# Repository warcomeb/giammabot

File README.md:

# giammabot
GiammaBot - Our family battle robot! :)

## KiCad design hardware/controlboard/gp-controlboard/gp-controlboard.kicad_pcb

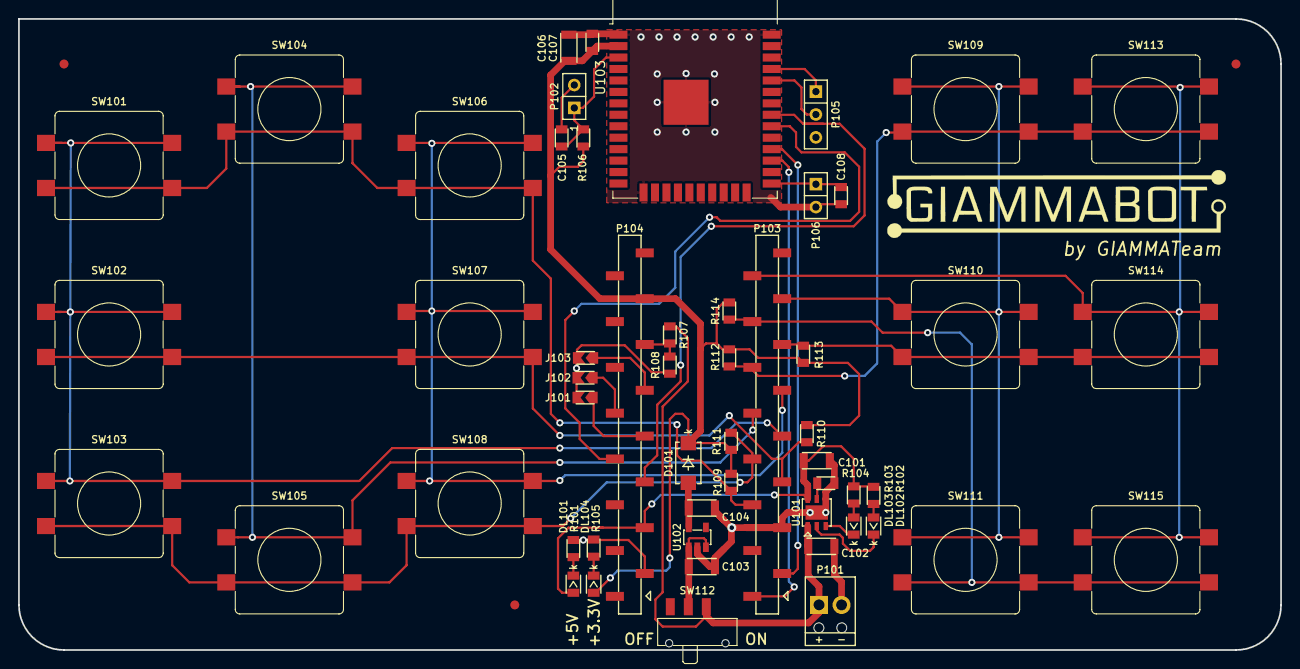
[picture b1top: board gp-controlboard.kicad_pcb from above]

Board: 2 copper layers, 140.0 x 70.0 mm, 57 parts (0 on the bottom side), 36 nets.

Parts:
C101, C102: 4u7; CAPACITOR-1206
C103, C104: 1u; CAPACITOR-1206
C105, C107, C108: 100n; CAPACITOR-0805
C106: 10u; CAPACITOR-1206
D101: MBRA340T3G; DIODE-DO214AC-UNI
DL101, DL104: GREEN; LED-0805
DL102, DL103: RED; LED-0805
J101, J102, J103: JUMPER-2_1; JUMPERSMD-2-0805
P101: BATTERY; CONN-MPT0.5_2-2.54
P102: EN_JMP; CONN-STRIP-2x1-2.54
P103: NUCLEO-CN3; SOCKET_16x1_2.54_SMD-WE-61001611921
P104: NUCLEO-CN4; SOCKET_16x1_2.54_SMD-WE-61001611921
P105: ESP_PROG; CONN-STRIP-3x1-2.54
P106: BOOT_JMP; CONN-STRIP-2x1-2.54
R101, R105: 330; RESISTOR-0805
R102, R103: 270; RESISTOR-0805
R104, R107, R108: TBD; RESISTOR-0805
R106, R109, R110, R111, R112, R113, R114: 10k; RESISTOR-0805
SW101, SW102, SW103, SW104, SW105, SW106, SW107, SW108, SW109, SW110, SW111, SW113, SW114, SW115: 430162073826; BUTTON-WE-430162073826
SW112: 450405020524; SWITCH-SPDT-WURTH-450405020524
U101: STBC08PMR; DFN6_3.0x3.0_1.0
U102: TLV70233DBV; SOT23-5
U103: ESP32-WROOM-32E(8MB); ESP32-WROOM-32D
VAL**: FIDUCIALMARK_1MM_3MM
VAL**#2, VAL**#3: FIDUCIALMARK_1MM_3MM

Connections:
+3.3V: C106.2, C107.1, D101.1, DL104.1, P104.14, R106.1, R109.1, R110.1, R111.1, R112.1, R113.1, R114.1, U103.2
+5V: C101.1, DL101.1, P104.4, R102.1, R103.1, U101.6
+VBAT: C102.1, P101.1, R107.2, SW112.3, U101.1
/ADC_BAT_STATUS: P104.12, R107.1, R108.2
/ADDR_0: J101.2, P104.8
/ADDR_1: J102.2, P104.9
/ADDR_2: J103.2, P104.10
/DIRECTION_C1: P103.8, SW101.1, SW101.2, SW102.1, SW102.2, SW103.1, SW103.2
/DIRECTION_C2: P103.9, SW104.1, SW104.2, SW105.1, SW105.2
/DIRECTION_C3: P103.10, SW106.1, SW106.2, SW107.1, SW107.2, SW108.1, SW108.2
/DIRECTION_R1: P103.5, R109.2, SW101.3, SW101.4, SW104.3, SW104.4, SW106.3, SW106.4
/DIRECTION_R2: P103.6, R110.2, SW102.3, SW102.4, SW107.3, SW107.4
/DIRECTION_R3: P103.7, R111.2, SW103.3, SW103.4, SW105.3, SW105.4, SW108.3, SW108.4
/ESP2MCU_01: P104.6, U103.31
/ESP2MCU_02: P104.7, U103.30
/ESP_BOOT: C108.2, P106.1, U103.25
/ESP_ENABLE: C105.2, P102.1, R106.2, U103.3
/ESP_PROG_RX: P105.2, U103.34
/ESP_PROG_TX: P105.1, U103.35
/POWER_C1: P103.14, SW109.1, SW109.2, SW110.1, SW110.2, SW111.1, SW111.2
/POWER_C2: P103.15, SW113.1, SW113.2, SW114.1, SW114.2, SW115.1, SW115.2
/POWER_R1: P103.11, R112.2, SW109.3, SW109.4, SW113.3, SW113.4
/POWER_R2: P103.12, R113.2, SW110.3, SW110.4, SW114.3, SW114.4
/POWER_R3: P103.13, R114.2, SW111.3, SW111.4, SW115.3, SW115.4
/UART_CMD_RX: P103.2, U103.28
/UART_CMD_TX: P103.1, U103.27
GND: C101.2, C102.2, C103.2, C104.2, C105.1, C106.1, C107.2, C108.1, J101.1, J102.1, J103.1, P101.2, P102.2, P103.4, P104.2, P105.3, P106.2, R101.1, R104.2, R105.1, R108.1, U101.4, U101.7, U102.2, U103.1, U103.15, U103.38, U103.39
unnamed: C103.1, SW112.2, U102.1, U102.3
unnamed: C104.1, D101.2, U102.5
unnamed: DL101.2, R101.2
unnamed: DL102.1, R102.2
unnamed: DL102.2, U101.2
unnamed: DL103.1, R103.2
unnamed: DL103.2, U101.3
unnamed: DL104.2, R105.2
unnamed: R104.1, U101.5

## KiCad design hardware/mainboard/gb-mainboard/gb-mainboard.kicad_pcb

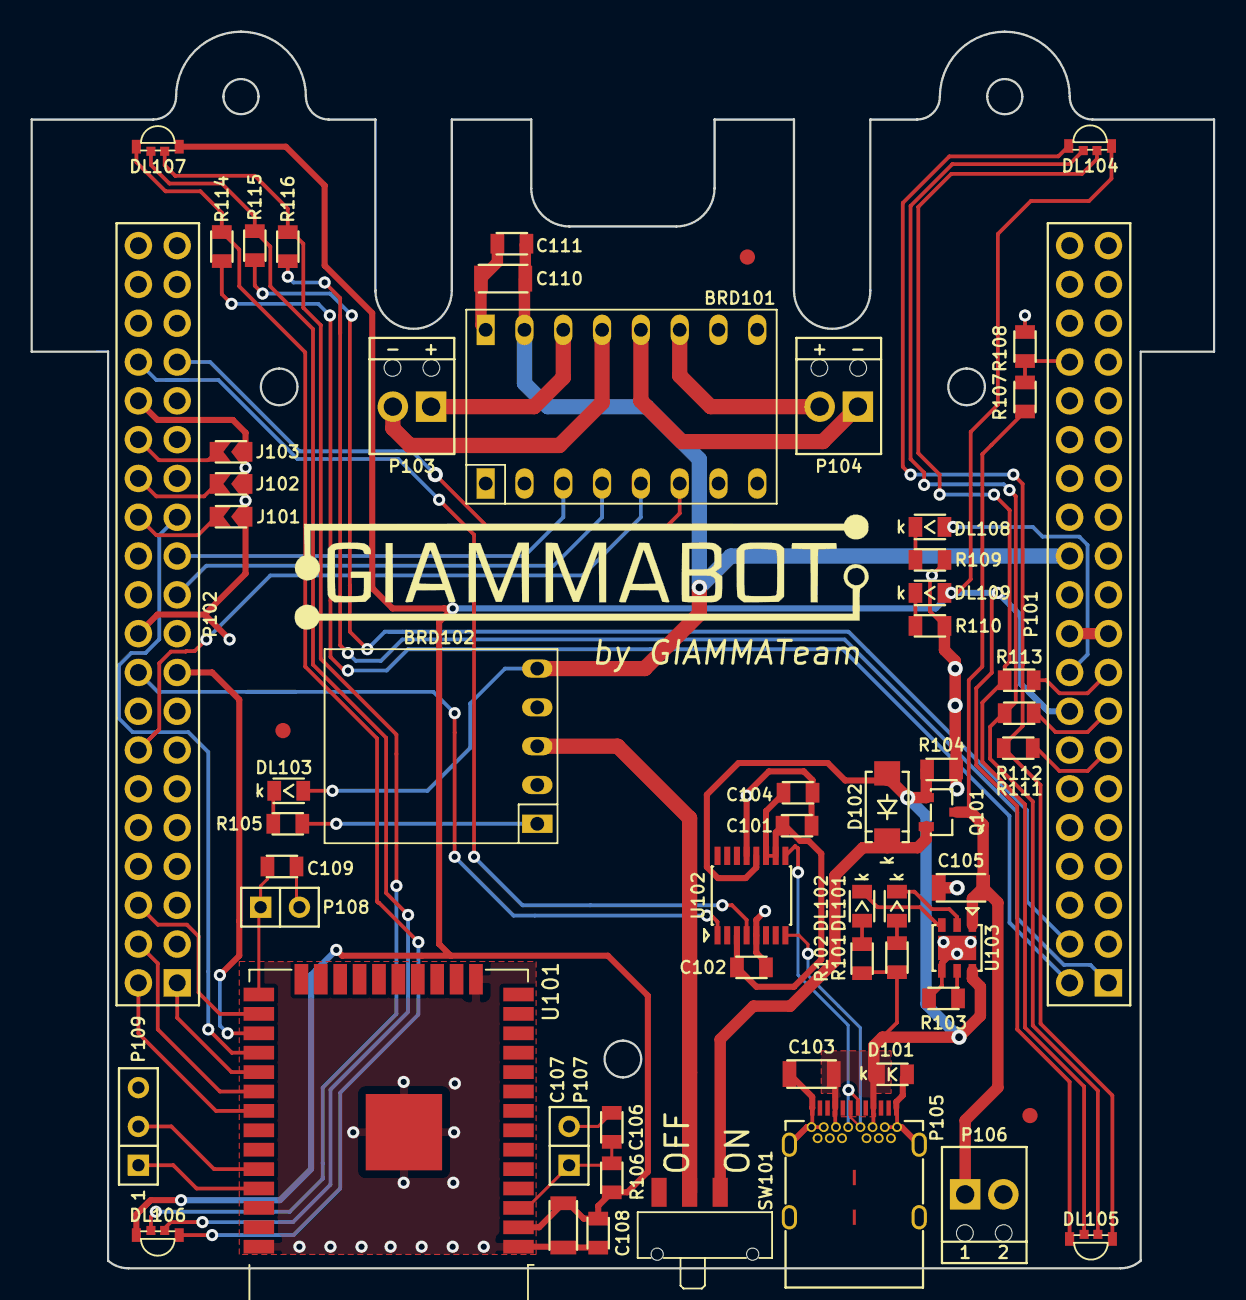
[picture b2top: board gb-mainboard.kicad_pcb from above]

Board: 2 copper layers, 77.4 x 81.0 mm, 60 parts (0 on the bottom side), 56 nets.

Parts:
BRD101: POLOLU-2130
BRD102: POLOLU-2868
C101, C102, C104, C106, C108, C109, C111: 100n; CAPACITOR-0805
C103, C105: 4u7; CAPACITOR-1206
C107, C110: 10u; CAPACITOR-1206
D101: ESDA25P35; DIODE-0805
D102: MBRA340T3G; DIODE-DO214AC-UNI
DL101, DL102, DL103: RED; LED-0805
DL104, DL105, DL106, DL107: 155124M173200; LEDRGB-WURTH-155124M173200
DL108, DL109: GREEN; LED-0805
J101, J102, J103: JUMPER-2_1; JUMPERSMD-2-0805
P101: NUCLEO-CN7; SOCKET_20x2_2.54-WE-61304021821
P102: NUCLEO-CN10; SOCKET_20x2_2.54-WE-61304021821
P103: MOTOR_SX; CONN-MPT0.5_2-2.54
P104: MOTOR_DX; CONN-MPT0.5_2-2.54
P105: WE-632723300011; USB3.1-C_WE-632723300011
P106: BATTERY; CONN-MPT0.5_2-2.54
P107: EN_JMP; CONN-STRIP-2x1-2.54
P108: BOOT_JMP; CONN-STRIP-2x1-2.54
P109: ESP_PROG; CONN-STRIP-3x1-2.54
Q101: DMP2120U-7; SOT23-3
R101, R102: 270; RESISTOR-0805
R103, R107, R108: TBD; RESISTOR-0805
R104, R106: 10k; RESISTOR-0805
R105, R109, R110: 330; RESISTOR-0805
R111, R112, R113, R114, R115, R116: 100; RESISTOR-0805
SW101: 450405020524; SWITCH-SPDT-WURTH-450405020524
U101: ESP32-WROOM-32E(8MB); ESP32-WROOM-32D
U102: FT230XS_2; SSOP16_3.9x4.9_0.635
U103: STBC08PMR; DFN6_3.0x3.0_1.0
VAL**: FIDUCIALMARK_1MM_3MM
VAL**#2, VAL**#3: FIDUCIALMARK_1MM_3MM

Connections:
+3.3V: C107.2, C108.1, DL104.1, DL105.1, DL106.1, DL107.1, DL109.1, P101.16, R106.1, U101.2
+5V: DL108.1, P101.18
+VBAT: C105.1, P106.1, Q101.3, R107.2, U103.1
+VIN: BRD101.15, BRD102.5, C110.2, C111.1, DL103.1, P101.24
+VUSB: C103.1, D101.1, D102.2, P105.A4, P105.A9, P105.B4, P105.B9, Q101.1, R101.1, R102.1, R104.1, U102.12, U103.6
/ADC_BAT_STATUS: P101.34, R107.1, R108.2
/ADDR_0: J101.1, P102.26
/ADDR_1: J102.1, P102.28
/ADDR_2: J103.1, P102.30
/ESP2MCU_01: P102.2, U101.31
/ESP2MCU_02: P102.4, U101.30
/ESP2MCU_03: P102.1, U101.29
/ESP2MCU_04: P102.6, U101.26
/ESP_BOOT: C109.2, P108.1, U101.25
/ESP_ENABLE: C106.2, P107.1, R106.2, U101.3
/ESP_PROG_RX: P109.2, U101.34
/ESP_PROG_TX: P109.1, U101.35
/LED_LX_BLUE: P101.1, R116.1
/LED_LX_GREEN: P101.4, R115.1
/LED_LX_RED: P101.2, R114.1
/LED_RX_BLUE: P101.17, R113.1
/LED_RX_GREEN: P101.15, R112.1
/LED_RX_RED: P101.13, R111.1
/MOTOR_DX_CTR1: BRD101.6, P102.33
/MOTOR_DX_CTR2: BRD101.5, P102.14
/MOTOR_SX_CTR1: BRD101.3, P102.23
/MOTOR_SX_CTR2: BRD101.4, P102.21
/UART_CMD_RX: P102.25, U101.28
/UART_CMD_TX: P102.17, U101.27
/UART_DBG_RX: P102.18, U102.1
/UART_DBG_TX: P102.34, U102.4
/USB_DM: P105.A7, P105.B7, U102.9
/USB_DP: P105.A6, P105.B6, U102.8
GND: BRD101.1, BRD101.16, BRD102.4, C101.2, C102.2, C103.2, C104.2, C105.2, C106.1, C107.1, C108.2, C109.1, C110.1, C111.2, D101.2, J101.2, J102.2, J103.2, P101.8, P101.19, P101.20, P101.22, P102.9, P102.20, P102.32, P105.A1, P105.A12, P105.B1, P105.B12, P105.S1, P106.2, P107.2, P108.2, P109.3, R103.2, R104.2, R108.1, R109.2, R110.2, U101.1, U101.15, U101.38, U101.39, U102.5, U102.13, U103.4, U103.7
unnamed: BRD101.11, P104.2
unnamed: BRD101.12, P104.1
unnamed: BRD101.13, P103.2
unnamed: BRD101.14, P103.1
unnamed: BRD102.1, R105.2
unnamed: BRD102.3, SW101.2
unnamed: C101.1, C102.1, C104.1, U102.3, U102.10, U102.11
unnamed: D102.1, Q101.2, SW101.3
unnamed: DL101.1, R101.2
unnamed: DL101.2, U103.2
unnamed: DL102.1, R102.2
unnamed: DL102.2, U103.3
unnamed: DL103.2, R105.1
unnamed: DL104.2, DL105.2, R113.2
unnamed: DL104.3, DL105.3, R112.2
unnamed: DL104.4, DL105.4, R111.2
unnamed: DL106.2, DL107.2, R116.2
unnamed: DL106.3, DL107.3, R115.2
unnamed: DL106.4, DL107.4, R114.2
unnamed: DL108.2, R109.1
unnamed: DL109.2, R110.1
unnamed: R103.1, U103.5

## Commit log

2021-03-09 Starting main board project
2021-03-16 started placing some components
2021-03-18 Working on USB: battery charger, communications and step-up
2021-03-20 motor driver connection and ESP connection.
2021-03-20 Esp programming.
2021-03-21 Added LEDs
2021-03-21 Ended schematic
2021-03-21 Working on PCB
2021-03-24 Fixed PCB. Logo missing.
2021-03-25 Starting remote control PCB
2021-03-30 [ControlBoard] Working on power supply...
2021-03-30 [ControlBoard] fixed power supply.
2021-04-01 Started PCB
2021-04-01 Working on PCB, placed almost all the components
2021-04-01 Place buttons
2021-04-03 Added connection to nucleo board. Working on PCB
2021-04-06 Added jumper for board address into control board. Ended PCB
2021-04-07 Added address jumper.
2021-04-08 Fixed silkscreen main board
2021-04-08 Added gerber file of mainboard
2021-04-08 Fixed silkscreen of control board
2021-04-09 Added gerber file of controlboard
2021-12-08 Added external project libraries.
2021-12-08 Startup project
2021-12-08 Added license
2021-12-12 Added TurnLight class
2021-12-18 Started working on motor control
2021-12-18 Working on motor driver class.
2021-12-22 Added function to TurnLight class. Must be implemented.
2021-12-22 Added Robot class: it used to manage all robot functionality.
2021-12-29 Fixed and tested motor driver.
2023-06-28 WiP: Added project of rev1
2023-06-29 Split scheme into pages
2023-06-29 Added line-follower project
2023-07-18 Modified driver motor
2023-07-18 Small fix
